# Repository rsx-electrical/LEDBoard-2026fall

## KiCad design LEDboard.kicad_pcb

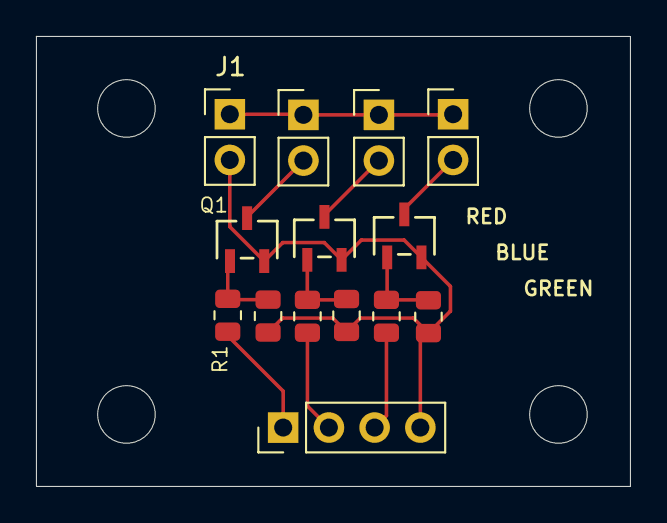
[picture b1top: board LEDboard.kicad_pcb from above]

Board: 2 copper layers, 33.0 x 25.0 mm, 18 parts (0 on the bottom side), 11 nets.

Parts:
H1, H2, H3, H4: MountingHole_3.2mm
J1: 24V_INPUT; PinHeader_1x02_P2.54mm_Vertical
J2: GPIO_INPUT; PinHeader_1x04_P2.54mm_Vertical
J3: RED_LAMP; PinHeader_1x02_P2.54mm_Vertical
J4: BLUE_LAMP; PinHeader_1x02_P2.54mm_Vertical
J5: GREEN_LAMP; PinHeader_1x02_P2.54mm_Vertical
Q1, Q2, Q3: AO3400A; SOT-23-3L_AOS
R1, R3, R5: 330; R_0805_2012Metric
R2, R4, R6: 100k; R_0805_2012Metric

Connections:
+24V: J1.1, J3.1, J4.1, J5.1
/GPIO_B: J2.2, R3.2
/GPIO_G: J2.3, R5.2
/GPIO_R: J2.1, R1.2
GND: J1.2, J2.4, Q1.2 (S), Q2.2 (S), Q3.2 (S), R2.2, R4.2, R6.2
unnamed: J3.2, Q1.3 (D)
unnamed: J4.2, Q2.3 (D)
unnamed: J5.2, Q3.3 (D)
unnamed: Q1.1 (G), R1.1, R2.1
unnamed: Q2.1 (G), R3.1, R4.1
unnamed: Q3.1 (G), R5.1, R6.1
